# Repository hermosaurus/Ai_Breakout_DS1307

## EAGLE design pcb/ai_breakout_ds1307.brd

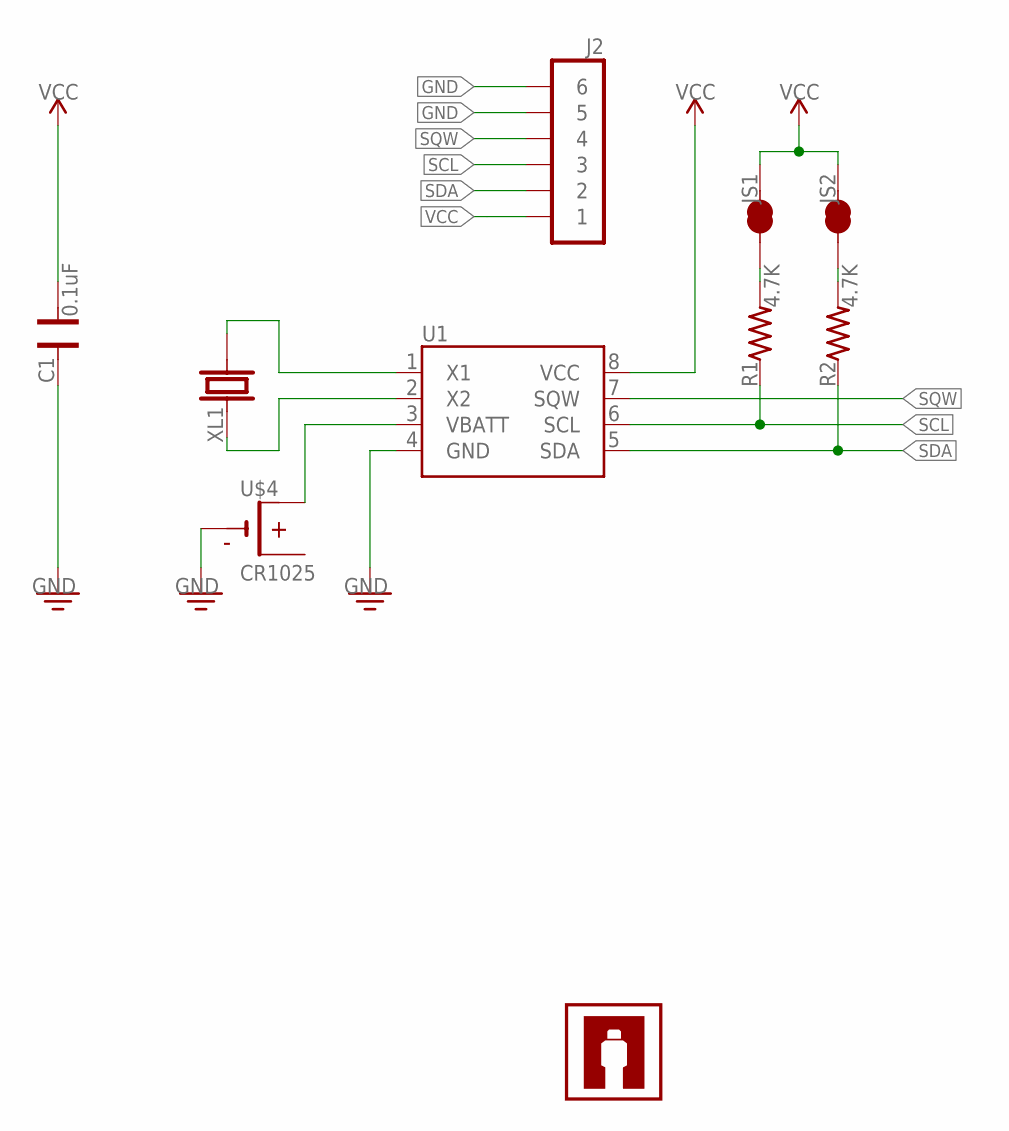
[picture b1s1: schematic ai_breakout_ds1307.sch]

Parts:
C1: 0.1uF; CAP-0603
J2: 1X06
JS1, JS2: 1X02-SJ-NCT
R1, R2: 4.7K; RES-0603
U1: DS1307SO8; SO08
U$3: AI-LOGOXS; AI-LOGO-XS
U$4: CR1025; CR1025-SMD
XL1: CRYSTALCYL-2X6MM-SMT; CRYSTAL-CYL-2X6MM-SMT

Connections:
GND: C1.2, J2.5, J2.6, U1.4 (GND), U$4.-
unnamed: JS1.1, R1.2
unnamed: JS2.1, R2.2
unnamed: U1.3 (VBATT), U$4.+@1 (+1), U$4.+@2 (+1)
unnamed: U1.2 (X2), XL1.1
unnamed: U1.1 (X1), XL1.2
SCL: J2.3, R1.1, U1.6 (SCL)
SDA: J2.2, R2.1, U1.5 (SDA)
SQW: J2.4, U1.7 (SQW)
VCC: C1.1, J2.1, JS1.2, JS2.2, U1.8 (VCC)

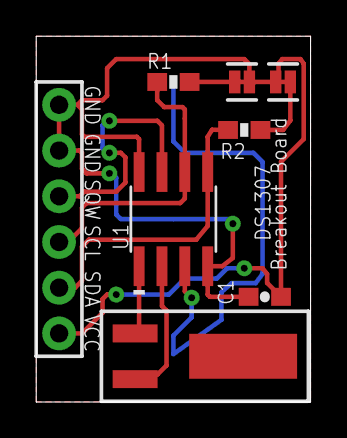
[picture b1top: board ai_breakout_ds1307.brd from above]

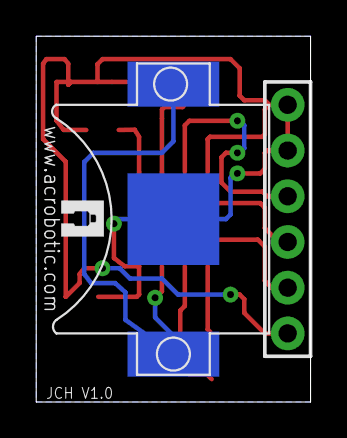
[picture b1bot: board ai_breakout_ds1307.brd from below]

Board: 2 copper layers, 15.2 x 20.3 mm, 10 parts (2 on the bottom side), 10 nets.

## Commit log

2015-06-24 board updated
